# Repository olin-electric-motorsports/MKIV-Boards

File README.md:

# MKIV

```
$ vagrant up
$ vagrant ssh
```

```
$ kicad
```

```
$ freecad
```

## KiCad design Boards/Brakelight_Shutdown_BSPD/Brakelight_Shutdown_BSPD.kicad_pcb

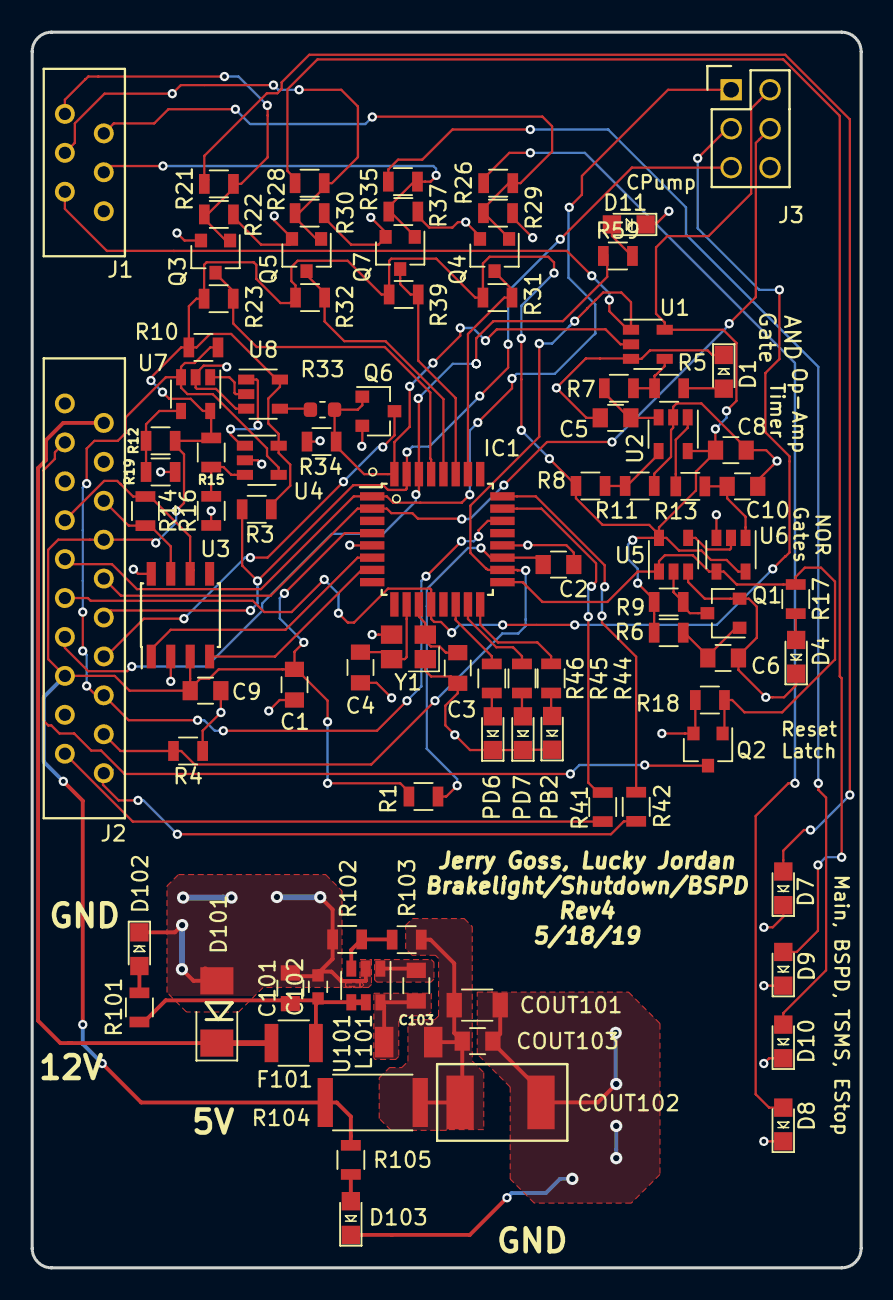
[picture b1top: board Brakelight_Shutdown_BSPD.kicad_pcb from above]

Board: 2 copper layers, 54.1 x 80.6 mm, 94 parts (0 on the bottom side), 66 nets.

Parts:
C1, C6, C8, C9, C101, C103: C_0.1uF; C_0805_OEM
C2: C_100pF; C_0805_OEM
C3, C4: C_30pF; C_0805_OEM
C5: C_10uF; C_0805_OEM
C10: C_1uF; C_0805_OEM
C102: C_2.2uF; C_0603
COUT101: C_22uF; C_1206_OEM
COUT102: C_33uF; Fuse_1812
COUT103: C_47uF; C_0805_OEM
D1, D4, D5, D7, D8, D9, D10, D11, D12, D13, D102, D103: LED_0805; LED_0805_OEM
D101: D_Zener_18V; DO-214AA
F101: F_500mA_16V; Fuse_1210
IC1: ATMEGA16M1; TQFP-32_7x7mm_Pitch0.8mm
J1: MM_F_RA_06; micromatch_female_ra_6
J2: MM_F_RA_20; micromatch_female_ra_20
J3: CONN_02X03; Pin_Header_Straight_2x03
L101: L_100uH
Q1, Q2, Q3, Q4, Q5, Q6, Q7: SSM3K333R; SOT-23F
R1: R_100; R_0805_OEM
R3: R_10k; R_0805_OEM
R4, R9, R22, R29, R30, R37, R103: R_100K; R_0805_OEM
R5, R14, R17, R41, R42, R44, R45, R46, R59, R101, R105: R_200; R_0805_OEM
R6, R8, R10, R11, R13, R15, R18, R23, R31, R32, R34, R39: R_10K; R_0805_OEM
R7: R_71.5K; R_0805_OEM
R12: R_2.2K; R_0805_OEM
R16, R21, R26, R28, R35: R_1K; R_0805_OEM
R19: R_499; R_0805_OEM
R33: R_0; R_0603_1608Metric
R102: R_25K; R_0805_OEM
R104: R_0_2512; R_2512_OEM
U1: SN74LVC1G08; SOT-23-5_OEM
U2, U4, U7: MCP6001; SOT-23-5_OEM
U3: CAN_Transceiver; SOIC-8_3.9x4.9mm_Pitch1.27mm_OEM
U5, U6: SN74LVC1G02; SOT-23-5_OEM
U8: SN74LVC1G32; SOT-23-5_OEM
U101: TPS560430YF; SOT-23-6_OEM
Y1: Crystal_SMD; Crystal_SMD_FA238

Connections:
+12V: D101.1, F101.2, J2.2
/BSPD_Current_Sense: IC1.18, J1.5, J2.18, R4.2, U1.1
/BSPD_Relay: J2.3, Q2.3
/BSPD_Relay_Sense: IC1.17, Q2.1, R17.1, R18.1, U5.1, U6.4
/Brake_Pressure_Sense: IC1.22, J2.16, R10.2, U4.4, U7.3
/Brakelight_Gate: IC1.32, Q6.1, R33.1, R34.1, U1.2
/Brakelight_LSD: J2.14, Q6.3
/CAN_high: J2.6, R14.1, U3.7
/CAN_low: J2.7, R14.2, U3.6
/Cooling_Pump_LSD: IC1.30, J2.13, R59.1
/LED_1: IC1.14, R46.1
/LED_2: IC1.15, R45.1
/LED_3: IC1.16, R44.1
/MISO: IC1.1, J2.9, J3.1
/MOSI: IC1.2, J2.10, J3.4
/RESET: IC1.31, J2.12, J3.5, R3.2
/RJ45_LED1: J2.19, R41.1
/RJ45_LED2: J2.20, R42.2
/RXCAN: IC1.7, U3.4
/SCK: IC1.12, J2.11, J3.3
/SS_BSPD_Pin: IC1.28, Q5.3, R32.2
/SS_E-Stop_Pin: IC1.26, Q4.3, R31.2
/SS_Main_Shutdown_Pin: IC1.29, Q3.3, R23.2
/SS_TSMS_Pin: IC1.27, Q7.3, R39.2
/Shutdown_Sense_BSPD: J1.3, Q5.1, R28.1, R30.1
/Shutdown_Sense_Estop: J1.2, Q4.1, R26.1, R29.1
/Shutdown_Sense_GLVMS: J1.1, Q3.1, R21.1, R22.1
/Shutdown_Sense_TSMS: J1.4, Q7.1, R35.1, R37.1
/TXCAN: IC1.6, U3.1
GND: C1.2, C2.2, C3.2, C4.2, C5.2, C6.2, C8.2, C9.2, C10.2, C101.2, C102.2, COUT101.2, COUT102.2, COUT103.2, D1.1, D4.1, D5.1, D7.1, D8.1, D9.1, D10.1, D11.1, D12.1, D13.1, D101.2, D102.1, D103.1, IC1.5, IC1.20, J2.1, J2.17, J3.6, Q1.2, Q2.2, Q3.2, Q4.2, Q5.2, Q6.2, Q7.2, R4.1, R11.2, R16.2, R18.2, R19.1, R22.2, R29.2, R30.2, R34.2, R37.2, R102.2, U1.3, U2.2, U3.2, U3.8, U4.2, U5.3, U6.3, U7.2, U8.3, U101.2, Y1.2, Y1.4
unnamed: C2.1, IC1.19, R1.2
unnamed: C3.1, IC1.11, Y1.1
unnamed: C4.1, IC1.10, Y1.3
unnamed: C5.1, R7.2, U2.3
unnamed: C6.1, Q1.1, R6.2
unnamed: C10.1, R13.1, U6.1
unnamed: C101.1, C102.1, F101.1, R101.1, U101.4, U101.5
unnamed: C103.1, L101.1, U101.6
unnamed: C103.2, U101.1
unnamed: COUT101.1, COUT102.1, COUT103.1, L101.2, R103.1, R104.1
unnamed: D1.2, R5.2
unnamed: D4.2, R17.2
unnamed: D5.2, R44.2
unnamed: D7.2, R21.2
unnamed: D8.2, R26.2
unnamed: D9.2, R28.2
unnamed: D10.2, R35.2
unnamed: D11.2, R59.2
unnamed: D12.2, R45.2
unnamed: D13.2, R46.2
unnamed: D102.2, R101.2
unnamed: D103.2, R105.2
unnamed: IC1.23, R41.2
unnamed: IC1.24, R42.1
unnamed: Q1.3, R9.1, U5.2
unnamed: R5.1, R7.1, U1.4
unnamed: R8.2, R11.1, U2.4
unnamed: R12.1, R19.2, U7.4
unnamed: R13.2, U2.1
unnamed: R15.2, R16.1, U4.3
unnamed: R33.2, U8.4
unnamed: R102.1, R103.2, U101.3
unnamed: U4.1, U8.1
unnamed: U5.4, U6.2
unnamed: U7.1, U8.2
VCC: C1.1, C8.1, C9.1, IC1.4, J2.8, J2.15, J3.2, R1.1, R3.1, R6.1, R8.1, R9.2, R10.1, R12.2, R15.1, R23.1, R31.1, R32.1, R39.1, R104.2, R105.1, U1.5, U2.5, U3.3, U4.5, U5.5, U6.5, U7.5, U8.5

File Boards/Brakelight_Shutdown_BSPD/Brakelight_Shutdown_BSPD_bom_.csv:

Component,Description,Part,References,Value,Footprint,Quantity Per PCB,Datasheet,Package,MPN,MFN,PurchasingLink,Link,Digi-key Part Number,Purchasing Link
1,"Capacitor, 0.1uF, 50V, 5%, 0805",C_0.1uF,C1 C6 C8 C9 C101 C103,C_0.1uF,C_0805_OEM,6,http://datasheets.avx.com/X7RDielectric.pdf,Value,478-3352-1-ND,Digi-Key DK,https://www.digikey.com/products/en?keywords=478-3352-1-ND,,,
2,"Capacitor, 100pF, 50V, 5%, 0805",C_100pF,C2,C_100pF,C_0805_OEM,1,https://content.kemet.com/datasheets/KEM_C1003_C0G_SMD.pdf,Value,399-1122-1-ND,Digi-Key,https://www.digikey.com/product-detail/en/kemet/C0805C101J5G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,,,
3,"Capacitor, 10uF, 10V, 10%, 0805",C_10uF,C5,C_10uF,C_0805_OEM,1,http://www.samsungsem.com/kr/support/product-search/mlcc/__i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,,1276-1052-1-ND,DK,https://www.digikey.com/product-detail/en/samsung-electro-me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,,,
4,"Capacitor, 1uF, 25V, 10%, 0805",C_1uF,C10,C_1uF,C_0805_OEM,1,http://www.samsungsem.com/kr/support/product-search/mlcc/__i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,,1276-2887-1-ND,DK,https://www.digikey.com/product-detail/en/samsung-electro-me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,,,
5,"Capacitor, 2.2uF, 10V, 10%, 0603",C_2.2uF,C102,C_2.2uF,C_0603_1608Metric,1,http://www.yageo.com/documents/recent/UPY-GPHC_X5R_4V-to-50V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,,311-1451-1-ND,DK,https://www.digikey.com/product-detail/en/yageo/CC0603KRX5R6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,,,
6,"Capacitor, 30pF, 50V, 5%, 0805",C_30pF,C3 C4,C_30pF,C_0805_OEM,2,https://media.digikey.com/pdf/Data%20Sheets/Samsung%20PDFs/C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,Value,1276-1130-1-ND,Digi-Key,https://www.digikey.com/product-detail/en/samsung-electro-me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,,,
7,"Capacitor, 22uF, 16V, 20%, 1206",C_22uF,COUT101,C_22uF,C_1206_OEM,1,https://product.tdk.com/info/en/catalog/datasheets/mlcc_comm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,,445-11693-1-ND,DK,https://www.digikey.com/product-detail/en/tdk-corporation/C3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,,,
8,,C_33uF,COUT102,C_33uF,Fuse_1812,1,https://product.tdk.com/info/en/catalog/datasheets/mlcc_comm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,,445-3924-1-ND,C4532X7R1C336M250KC,https://www.digikey.com/product-detail/en/tdk-corporation/C4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,,,
9,"Capacitor, 47uF, 6.3V, 20%, 0805",C_47uF,COUT103,C_47uF,C_0805_OEM,1,http://www.samsungsem.com/kr/support/product-search/mlcc/__i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,,1276-6467-1-ND,DK,https://www.digikey.com/product-detail/en/samsung-electro-me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,,,
10,"Diode, Zener, 18V, 5W, 5%",D_Zener_18V,D101,D_Zener_18V,DO-214AA,1,http://www.mccsemi.com/up_pdf/SMBJ5338B-SMBJ5388B(SMB).pdf,,SMBJ5355B-TPMSCT-ND,DK,https://www.digikey.com/products/en?keywords=SMBJ5355B-TPMSCT-ND,,,
11,"LED, Green, 2.2V, 20mA, 0805",LED_0805,D1 D4 D5 D7 D8 D9 D10 D11 D12 D13 D102 D103,LED_0805,LED_0805_OEM,12,http://www.osram-os.com/Graphics/XPic9/00078860_0.pdf,,475-1410-1-ND,DK,https://www.digikey.com/products/en?keywords=475-1410-1-ND,,,
12,"Fuse, PTC, 500mA, 16V, 1210",F_500mA_16V,F101,F_500mA_16V,Fuse_1210,1,https://belfuse.com/resources/CircuitProtection/datasheets/0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,,507-1786-1-ND,DK,https://www.digikey.com/product-detail/en/bel-fuse-inc/0ZCH0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,,,
13,"Microcontroller, 8-bit, 1KB RAM, 16KB Flash",ATMEGA16M1,IC1,ATMEGA16M1,TQFP-32_7x7mm_Pitch0.8mm,1,http://www.atmel.com/Images/Atmel-8209-8-bit%20AVR%20ATmega1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,Value,ATMEGA16M1-AU-ND,Digi-Key,https://www.digikey.com/product-detail/en/atmel/ATMEGA16M1-A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,,,
14,"Connector header through hole 2x3 0.100"" (2.54mm)",CONN_02X03,J3,CONN_02X03,Pin_Header_Straight_2x03,1,http://portal.fciconnect.com/Comergent//fci/drawing/67996.pdf,Value,609-3234-ND,Digi-Key,https://www.digikey.com/product-detail/en/amphenol-fci/67997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,,,
15,Micro-MaTch connector 6 pin female right angle,MM_F_RA_06,J1,MM_F_RA_06,micromatch_female_ra_6,1,http://www.te.com/commerce/DocumentDelivery/DDEController?Ac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,,338070-6,TE,http://www.te.com/usa-en/product-338070-6.html,,,
16,Micro-MaTch connector 20 pin female right angle,MM_F_RA_20,J2,MM_F_RA_20,micromatch_female_ra_20,1,http://www.te.com/commerce/DocumentDelivery/DDEController?Ac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,,2-338070-0,TE,http://www.te.com/usa-en/product-2-338070-0.html,,,
17,,L_100uH,L101,L_100uH,L_100uH,1,https://product.tdk.com/info/en/catalog/datasheets/inductor_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,,445-15759-1-ND,Digikey,,https://www.digikey.com/product-detail/en/tdk-corporation/NL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,,
18,"MOSFET, N-channel, 30V, 6A",SSM3K333R,Q1 Q2 Q3 Q4 Q5 Q6 Q7,SSM3K333R,SOT-23F,7,https://drive.google.com/drive/folders/0B-V-iZf33Y4GNzhDQTJZanJRbVk,,SSM3K333RLFCT-ND,DK,https://www.digikey.com/product-detail/en/toshiba-semiconduc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,,,
19,"Resistor, 0 ohm jumper, 0.1W, 0603",R_0,R33,R_0,R_0603_1608Metric,1,http://industrial.panasonic.com/www-cgi/jvcr13pz.cgi?E+PZ+3+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,,P0.0GCT-ND,DK,https://www.digikey.com/product-detail/en/panasonic-electron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,,,
20,"Resistor, 0 ohm jumper, 3W, 2512",R_0_2512,R104,R_0_2512,R_2512_OEM,1,http://www.te.com/commerce/DocumentDelivery/DDEController?Ac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,,A121322CT-ND,DK,https://www.digikey.com/products/en?keywords=A121322CT-ND,,,
21,"Resistor, 100, 0.25W, 1%, 0805",R_100,R1,R_100,R_0805_OEM,1,https://www.seielect.com/Catalog/SEI-rncp.pdf,Value,RNCP0805FTD100RCT-ND,Digi-Key,https://www.digikey.com/products/en?keywords=RNCP0805FTD100RCT-ND,,,
22,"Resistor, 100K, 0.125W, 1%, 0805",R_100K,R2 R4 R9 R22 R29 R30 R37 R103,R_100K,R_0805_OEM,8,https://industrial.panasonic.com/cdbs/www-data/pdf/RDA0000/A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,,P100KCCT-ND,DK,https://www.digikey.com/product-detail/en/panasonic-electron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,,,
23,"Resistor, 10K, 0.25W, 1%, 0805",R_10K,R3 R6 R8 R11 R13 R18 R23 R24 R25 R27 R31 R32 R34 R39,R_10k,R_0805_OEM,14,http://www.bourns.com/data/global/pdfs/CRS.pdf,Value,CRS0805-FX-1002ELFCT-ND,Digi-Key DK,https://www.digikey.com/products/en?keywords=CRS0805-FX-1002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,,,
24,"Resistor, 1K, 0.25W, 1%, 0805",R_1K,R21 R26 R28 R35,R_1K,R_0805_OEM,4,https://www.seielect.com/Catalog/SEI-rncp.pdf,,RNCP0805FTD1K00CT-ND,DK,https://www.digikey.com/products/en?keywords=RNCP0805FTD1K00CT-ND,,,
25,"Resistor, 200, 0.125W, 5%, 0805",R_200,R5 R14 R17 R41 R42 R44 R45 R46 R101 R105,R_200,R_0805_OEM,10,https://www.seielect.com/Catalog/SEI-RMCF_RMCP.pdf,Value,RMCF0805JT200RCT-ND,DK Digi-Key,https://www.digikey.com/products/en?keywords=RMCF0805JT200RCT-ND,,,
26,,R_25K,R102,R_25K,R_0805_OEM,1,https://www.te.com/commerce/DocumentDelivery/DDEController?A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,,,A124124CT-ND,https://www.digikey.com/product-detail/en/te-connectivity-pa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,,CPF-A-0805B25KE,
27,"Resistor, 1.07K, 0.125W, 0.1%, 0805",R_1.07K,R7,R_71.5K,R_0805_OEM,1,https://industrial.panasonic.com/cdbs/www-data/pdf/RDM0000/A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,,P1.07KDACT-ND,DK,,,,
28,"High speed CAN transceiver, 1Mb/s",MCP2561-E_SN,U3,CAN_Transceiver,SOIC-8_3.9x4.9mm_Pitch1.27mm_OEM,1,http://www.microchip.com/mymicrochip/filehandler.aspx?ddocna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,Value,MCP2561-E/SN-ND,Digi-Key,https://www.digikey.com/products/en?keywords=mcp2561-e%2Fsn,,,
29,"Op-amp, general purpose",MCP6001,U2 U7,MCP6001,SOT-23-5_OEM,2,http://ww1.microchip.com/downloads/en/DeviceDoc/21733j.pdf,,MCP6001T-I/OTCT-ND,DK,https://www.digikey.com/product-detail/en/microchip-technolo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,,,
30,Single channel positive logic NOR gate,SN74LVC1G02,U5 U6,SN74LVC1G02,SOT-23-5_OEM,2,http://www.ti.com/lit/ds/symlink/sn74lvc1g02.pdf,,296-11598-1-ND,DK,https://www.digikey.com/product-detail/en/texas-instruments/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,,,
31,Single channel positive logic AND gate,SN74LVC1G08,U1,SN74LVC1G08,SOT-23-5_OEM,1,http://www.ti.com/lit/ds/symlink/sn74lvc1g08.pdf,,296-11602-1-ND,DK,https://www.digikey.com/product-detail/en/texas-instruments/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,,,
32,,TPS560430YF,U101,TPS560430YF,SOT-23-6_Handsoldering,1,http://www.ti.com/lit/ds/symlink/tps560430.pdf,,TPS560430YFDBVR,TPS560430YFDBVR-ND,,,,https://www.digikey.com/product-detail/en/texas-instruments/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
33,CRYSTAL 16.0000MHZ 18PF SMD,Crystal_SMD,Y1,Crystal_SMD,Crystal_SMD_FA238,1,https://support.epson.biz/td/api/doc_check.php?dl=brief_FA-2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,Value,SER3686CT-ND,Digi-Key,https://www.digikey.com/products/en?keywords=SER3686CT-ND,,,





Component Groups:,33
Component Count:,90
Fitted Components:,90
Number of PCBs:,1
Total components:,90
Schematic Version:,
Schematic Date:,
BoM Date:,Thu 09 May 2019 08:50:00 PM EDT
Schematic Source:,/home/jerry/OlinCollege/Formula/MKIV-Boards/Boards/Brakelight_Shutdown_BSPD/Brakelight_Shutdown_BSPD.sch
KiCad Version:,Eeschema 5.0.2-bee76a0~70~ubuntu18.04.1

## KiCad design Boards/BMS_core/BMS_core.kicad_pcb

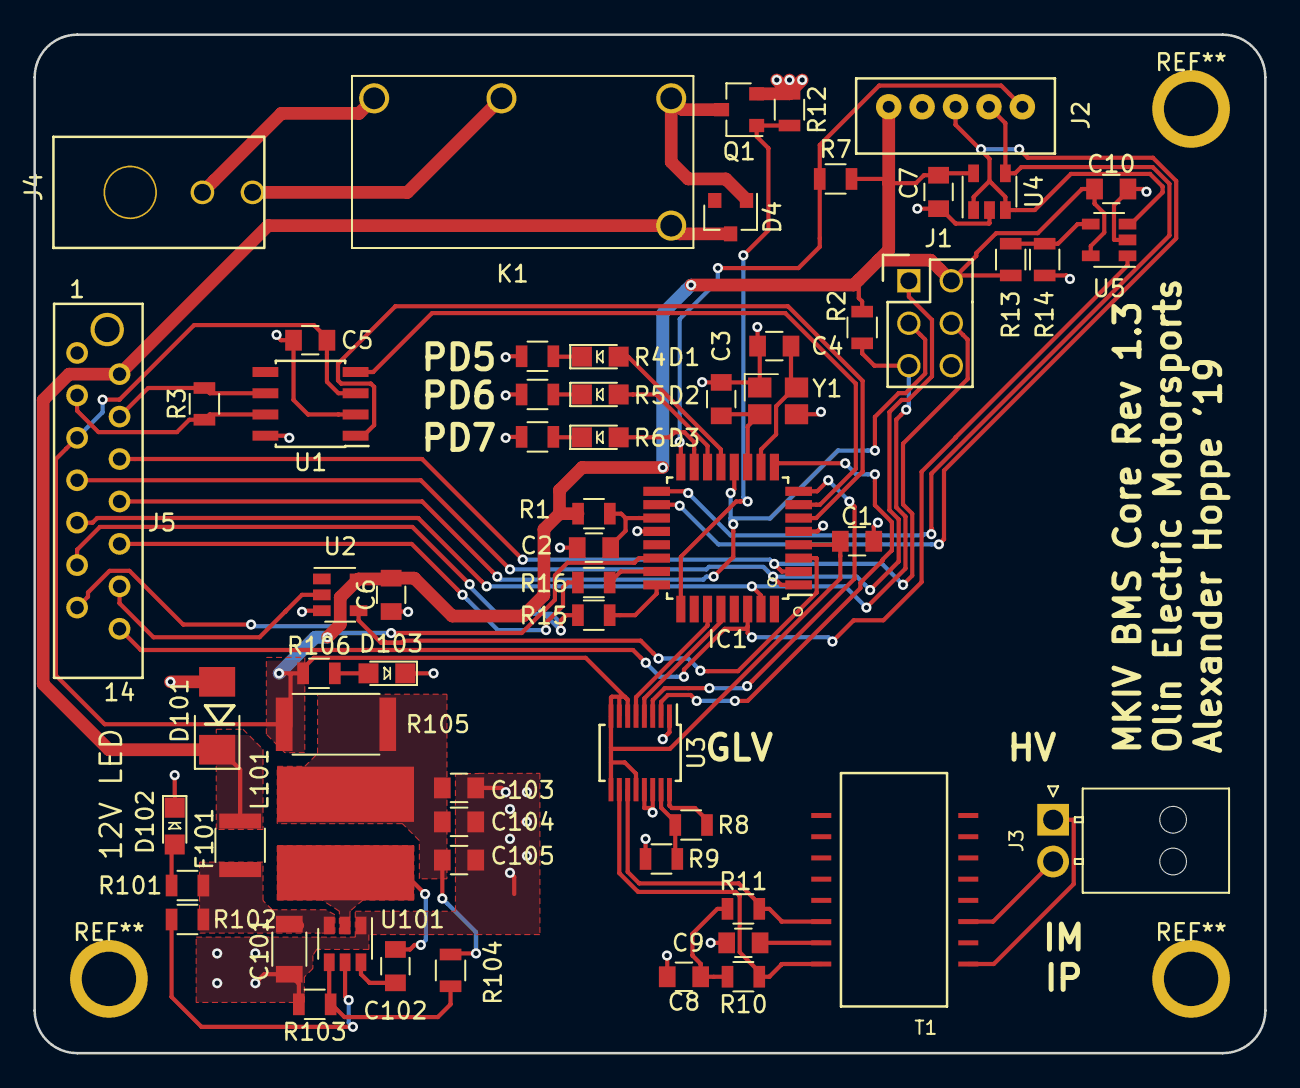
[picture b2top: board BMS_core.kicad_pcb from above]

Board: 2 copper layers, 73.7 x 61.0 mm, 62 parts (0 on the bottom side), 56 nets.

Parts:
C1, C5, C6, C7, C10, C102, C105: C_0.1uF; C_0805_OEM
C2: C_100pF; C_0805_OEM
C3, C4: C_30pF; C_0805_OEM
C8, C9: C_10nF; C_0805_OEM
C101: C_22uF; C_1206_OEM
C103: C_47uF; C_0805_OEM
C104: C_1uF; C_0805_OEM
D1, D2, D3, D102, D103: LED_0805; LED_0805_OEM
D4: BAS40-00; SOT-23
D101: D_Zener_18V; DO-214AA
F101: 500mA; Fuse_1210
IC1: ATMEGA16M1; TQFP-32_7x7mm_Pitch0.8mm
J1: CONN_02X03; Pin_Header_Straight_2x03
J2: B5B-PH-K-S
J3: NanoFit_2; NanoFit_Molex_1x02x2.50mm_Angled_OEM
J4: MicroFit_RA_V_2
J5: MM_F_VT_14; micromatch_female_vert_14
K1: G5Q-1A4-DC5-5V; Relay_SPST_OMRON-G5Q-1A4_OEM
L101: L_4.7uH; 4.7uH_Inductor_OEM
Q1: SSM3K333R; SOT-23F
R1: R_100; R_0805_OEM
R2, R7, R12, R102, R103: R_10K; R_0805_OEM
R3, R4, R5, R6, R15, R16, R106: R_200; R_0805_OEM
R8: R_3.01K; R_0805_OEM
R9, R101: R_1K; R_0805_OEM
R10, R11: R_60.4; R_0805_OEM
R13: R_17.4K_0.1; R_0805_OEM
R14: R_1K_0.1; R_0805_OEM
R104: R_54.9K; R_0805_OEM
R105: R_0_2512; R_2512_OEM
T1: T_LAN_7490100111A
U1: MCP2561-E_SN; SOIC-8_3.9x4.9mm_Pitch1.27mm_OEM
U2: SN74LVC1G17; SOT-23-5
U3: LTC6820HMS; MSOP-16_3x4mm_P0.5mm
U4, U5: MCP6001; SOT-23-5_OEM
U101: TPS561201; SOT-23-6_OEM
Y1: Crystal_SMD; Crystal_SMD_FA238

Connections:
+12V: D4.3, D101.1, F101.1, J5.2, K1.5
/BMS_SENSE: IC1.22, J5.13
/BSPD_CURRENT: IC1.30, J5.14, U5.1
/CANH: J5.3, R3.1, U1.7
/CANL: J5.4, R3.2, U1.6
/CS_iso: IC1.27, U3.5
/FAN_PWM: J5.12, U2.2
/FAN_PWM_RAW: IC1.3, U2.4
/MISO: IC1.1, J1.1, J5.7
/MISO_iso: IC1.8, U3.3
/MOSI: IC1.2, J1.4, J5.6
/MOSI_iso: IC1.9, U3.2
/PROG_1: D1.2, IC1.13
/PROG_2: D2.2, IC1.14
/PROG_3: D3.2, IC1.15
/RELAY_DRIVE: IC1.25, Q1.1, R12.2
/RESET: IC1.31, J1.5, J5.9, R2.2
/RJ45_LED1: J5.10, R16.1
/RJ45_LED2: J5.11, R15.1
/RXCAN: IC1.7, U1.4
/SCK: IC1.12, J1.3, J5.8
/SCK_iso: IC1.28, U3.4
/SHDN_IN(MAIN_PACK->BMS): J4.1, K1.3
/SHDN_OUT(BMS->IMD): J4.2, K1.2
/TXCAN: IC1.6, U1.1
/VOUT: IC1.18, J2.3, U4.1, U4.3, U5.3
/VREF: IC1.17, J2.4, U4.4
/~OCD: IC1.16, J2.5, R7.2
GND: C1.2, C2.2, C3.2, C4.2, C5.2, C6.1, C7.2, C8.2, C9.2, C10.2, C101.2, C103.2, C104.2, C105.2, D101.2, D102.1, D103.1, IC1.5, IC1.20, J1.6, J2.2, J5.1, Q1.2, R4.2, R5.2, R6.2, R9.2, R12.1, R14.2, R103.2, U1.2, U1.8, U2.3, U3.1, U3.13, U3.14, U4.2, U5.2, U101.1, Y1.2, Y1.4
unnamed: C2.1, IC1.19, R1.2
unnamed: C3.1, IC1.11, Y1.1
unnamed: C4.1, IC1.10, Y1.3
unnamed: C8.1, R10.2, R11.1
unnamed: C9.1, T1.15
unnamed: C101.1, F101.2, R101.1, R102.2, U101.3
unnamed: C102.1, U101.6
unnamed: C102.2, L101.1, U101.2
unnamed: C103.1, C104.1, C105.1, L101.2, R104.2, R105.2
unnamed: D1.1, R4.1
unnamed: D2.1, R5.1
unnamed: D3.1, R6.1
unnamed: D4.1, K1.1, Q1.3
unnamed: D102.2, R101.2
unnamed: D103.2, R106.2
unnamed: IC1.23, R16.2
unnamed: IC1.24, R15.2
unnamed: J3.1, T1.1
unnamed: J3.2, T1.3
unnamed: R8.1, U3.16
unnamed: R8.2, R9.1, U3.15
unnamed: R10.1, T1.16, U3.10
unnamed: R11.2, T1.14, U3.11
unnamed: R13.2, R14.1, U5.4
unnamed: R102.1, U101.5
unnamed: R103.1, R104.1, U101.4
VCC: C1.1, C5.1, C6.2, C7.1, C10.1, IC1.4, J1.2, J2.1, J5.5, R1.1, R2.1, R7.1, R13.1, R105.1, R106.1, U1.3, U2.5, U3.6, U3.7, U3.8, U3.9, U3.12, U4.5, U5.5

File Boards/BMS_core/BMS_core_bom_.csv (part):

Component,Description,Part,References,Value,Footprint,Quantity Per PCB,Datasheet,Package,MPN,MFN,PurchasingLink
1,"Capacitor, 0.1uF, 50V, 5%, 0805",C_0.1uF,C1 C5 C6 C7 C10 C102 C105,C_0.1uF,C_0805_OEM,7,http://datasheets.avx.com/X7RDielectric.pdf,Value,478-3352-1-ND,Digi-Key DK,https://www.digikey.com/products/en?keywords=478-3352-1-ND
2,"Capacitor, 100pF, 50V, 5%, 0805",C_100pF,C2,C_100pF,C_0805_OEM,1,https://content.kemet.com/datasheets/KEM_C1003_C0G_SMD.pdf,Value,399-1122-1-ND,Digi-Key,https://www.digikey.com/product-detail/en/kemet/C0805C101J5G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
3,"Capacitor, 10nF 50V X7R 0805",C_10nF,C8 C9,C_10nF,C_0805_OEM,2,http://www.samsungsem.com/kr/support/product-search/mlcc/__i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,,1276-1015-1-ND,DK,https://www.digikey.com/product-detail/en/samsung-electro-me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
4,"Capacitor, 1uF, 25V, 10%, 0805",C_1uF,C104,C_1uF,C_0805_OEM,1,http://datasheets.avx.com/X7RDielectric.pdf,Value,478-10487-1-ND,Digi-Key,https://www.digikey.com/product-detail/en/avx-corporation/08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
5,"Capacitor, 22uF, 16V, 20%, 1206",C_22uF,C101,C_22uF,C_1206_OEM,1,http://www.samsungsem.com/kr/support/product-search/mlcc/__i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,Value,1276-2725-1-ND,Digi-Key,https://www.digikey.com/products/en?keywords=1276-2725-1-ND
6,"Capacitor, 30pF, 50V, 5%, 0805",C_30pF,C3 C4,C_30pF,C_0805_OEM,2,https://media.digikey.com/pdf/Data%20Sheets/Samsung%20PDFs/C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,Value,1276-1130-1-ND,Digi-Key,https://www.digikey.com/product-detail/en/samsung-electro-me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
7,"Capacitor, 47uF, 6.3V, 20%, 0805",C_47uF,C103,C_47uF,C_0805_OEM,1,http://www.yuden.co.jp/productdata/catalog/en/mlcc_all_e.pdf,Value,587-4280-1-ND,Digi-Key,https://www.digikey.com/product-detail/en/taiyo-yuden/JMK212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
8,"Schottky Diode, 40V, 120mA, SOT23",BAS40-00,D4,BAS40-00,SOT-23,1,https://assets.nexperia.com/documents/data-sheet/BAS40_1PSXX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,,1727-4234-1-ND,DK,https://www.digikey.com/product-detail/en/nexperia-usa-inc/B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
9,"Diode, Zener, 18V, 5W, 5%",D_Zener_18V,D101,D_Zener_18V,DO-214AA,1,http://www.mccsemi.com/up_pdf/SMBJ5338B-SMBJ5388B(SMB).pdf,DO-214AA (SMB),SMBJ5355B-TPMSCT-ND,Digi-Key,https://www.digikey.com/products/en?keywords=SMBJ5355B-TPMSCT-ND
10,"LED, Green, 2.2V, 20mA, 0805",LED_0805,D1 D2 D3 D102 D103,LED_0805,LED_0805_OEM,5,http://www.osram-os.com/Graphics/XPic9/00078860_0.pdf,Value,475-1410-1-ND,DK Digi-Key,https://www.digikey.com/products/en?keywords=475-1410-1-ND
11,"Fuse, PTC, 500mA, 16V, 1210",F_500mA_16V,F101,500mA,Fuse_1210,1,https://belfuse.com/resources/CircuitProtection/datasheets/0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,Value,507-1786-1-ND,Digi-Key,https://www.digikey.com/product-detail/en/bel-fuse-inc/0ZCH0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
12,"Microcontroller, 8-bit, 1KB RAM, 16KB Flash",ATMEGA16M1,IC1,ATMEGA16M1,TQFP-32_7x7mm_Pitch0.8mm,1,http://www.atmel.com/Images/Atmel-8209-8-bit%20AVR%20ATmega1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,Value,ATMEGA16M1-AU-ND,Digi-Key,https://www.digikey.com/product-detail/en/atmel/ATMEGA16M1-A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
13,"Connector Header Through Hole 5 position 0.079"" (2.00mm)",B5B-PH-K-S,J2,B5B-PH-K-S,B5B-PH-K-S,1,http://www.jst-mfg.com/product/pdf/eng/ePH.pdf,,455-1707-ND,DK,https://www.digikey.com/product-detail/en/jst-sales-america-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
14,"Connector header through hole 2x3 0.100"" (2.54mm)",CONN_02X03,J1,CONN_02X03,Pin_Header_Straight_2x03,1,http://portal.fciconnect.com/Comergent//fci/drawing/67996.pdf,Value,609-3234-ND,Digi-Key,https://www.digikey.com/product-detail/en/amphenol-fci/67997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
15,Micro-MaTch connector 14 pin female vertical,MM_F_VT_14,J5,MM_F_VT_14,micromatch_female_vert_14,1,http://www.te.com/commerce/DocumentDelivery/DDEController?Ac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,,1-338068-4,TE,http://www.te.com/global-en/product-1-338068-4.html
16,"Micro-Fit Connector, Right Angle 2 circuit",MicroFit_RA_R_2,J4,MicroFit_RA_R_2,MicroFit_RA_2,1,https://www.molex.com/pdm_docs/sd/436500201_sd.pdf,,WM1865-ND,DK,https://www.digikey.com/product-detail/en/molex/0436500201/W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
17,Nano-Fit connector 2 pin right angle,NanoFit_2,J3,NanoFit_2,NanoFit_Molex_1x02x2.50mm_Angled_OEM,1,https://www.molex.com/pdm_docs/sd/1053131102_sd.pdf,,WM14972-ND,DK,https://www.digikey.com/products/en/connectors-interconnects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
18,"Relay, SPST-NO, Switch 10A/30V, Coil 40mA/5V",G5Q-1A4-DC5-5V,K1,G5Q-1A4-DC5-5V,Relay_SPST_OMRON-G5Q-1A4_OEM,1,http://omronfs.omron.com/en_US/ecb/products/pdf/en-g5q.pdf,,Z3632-ND,DK,https://www.digikey.com/product-detail/en/omron-electronics-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
19,"Inductor, 4.7uH, 4.4A, 25mOhm, 20%",L_4.7uH,L101,L_4.7uH,4.7uH_Inductor_OEM,1,https://product.tdk.com/info/en/documents/wdcatalog/withdraw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,Value,445-6583-1-ND,Digi-Key,https://www.digikey.com/product-detail/en/tdk-corporation/VL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
20,"MOSFET, N-channel, 30V, 6A",SSM3K333R,Q1,SSM3K333R,SOT-23F,1,https://drive.google.com/drive/folders/0B-V-iZf33Y4GNzhDQTJZanJRbVk,,SSM3K333RLFCT-ND,DK,https://www.digikey.com/product-detail/en/toshiba-semiconduc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
21,"Resistor, 0 ohm jumper, 3W, 2512",R_0_2512,R105,R_0_2512,R_2512_OEM,1,http://www.te.com/commerce/DocumentDelivery/DDEController?Ac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,,A121322CT-ND,DK,https://www.digikey.com/products/en?keywords=A121322CT-ND
22,"Resistor, 100, 0.25W, 1%, 0805",R_100,R1,R_100,R_0805_OEM,1,https://www.seielect.com/Catalog/SEI-rncp.pdf,Value,RNCP0805FTD100RCT-ND,Digi-Key,https://www.digikey.com/products/en?keywords=RNCP0805FTD100RCT-ND
23,"Resistor, 10K, 0.25W, 1%, 0805",R_10K,R2 R7 R12 R102 R103,R_10K,R_0805_OEM,5,http://www.bourns.com/data/global/pdfs/CRS.pdf,,CRS0805-FX-1002ELFCT-ND,DK,https://www.digikey.com/products/en?keywords=CRS0805-FX-1002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
24,"Resistor, 17.4K, 0.125W, 0.1%, 0805",R_17.4K_0.1,R13,R_17.4K_0.1,R_0805_OEM,1,https://industrial.panasonic.com/cdbs/www-data/pdf/RDM0000/A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,,P17.4KDACT-ND,DK,https://www.digikey.com/product-detail/en/panasonic-electron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
25,"Resistor, 1K, 0.25W, 1%, 0805",R_1K,R9 R101,R_1K,R_0805_OEM,2,https://www.seielect.com/Catalog/SEI-rncp.pdf,,RNCP0805FTD1K00CT-ND,DK,https://www.digikey.com/products/en?keywords=RNCP0805FTD1K00CT-ND
26,"Resistor, 1K, 0.125W, 0.1%, 0805",R_1K_0.1,R14,R_1K_0.1,R_0805_OEM,1,https://industrial.panasonic.com/cdbs/www-data/pdf/RDM0000/A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,,P1.0KDACT-ND,DK,https://www.digikey.com/product-detail/en/panasonic-electron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
27,"Resistor, 200, 0.125W, 5%, 0805",R_200,R3 R4 R5 R6 R106,R_200,R_0805_OEM,5,https://www.seielect.com/Catalog/SEI-RMCF_RMCP.pdf,Value,RMCF0805JT200RCT-ND,Digi-Key DK,https://www.digikey.com/products/en?keywords=RMCF0805JT200RCT-ND
28,"Resistor, 3.01K, 0.125W, 1%, 0805",R_3.01K,R8,R_3.01K,R_0805_OEM,1,http://www.yageo.com.tw/exep/pages/download/literatures/PYu-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,,311-3.01KCRCT-ND,DK,https://www.digikey.com/products/en?keywords=311-3.01KCRCT-ND
29,"Resistor, 54.9, 0.125W, 1%, 0805",R_54.9K,R104,R_54.9K,R_0805_OEM,1,https://industrial.panasonic.com/cdbs/www-data/pdf/RDA0000/A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,,311-54.9KCRCT-ND,DK,https://www.digikey.com/product-detail/en/yageo/RC0805FR-075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
30,"Resistor, 60.4, 0.1%, 0.125W, 0805",R_60.4,R10 R11,R_60.4,R_0805_OEM,2,https://industrial.panasonic.com/cdbs/www-data/pdf/RDM0000/A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,,P60.4DACT-ND,DK,https://www.digikey.com/product-detail/en/panasonic-electron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
31,Transformer LAN 10/100 base-T,T_LAN_7490100111A,T1,T_LAN_7490100111A,T_LAN_7490100111A,1,https://katalog.we-online.de/pbs/datasheet/7490100111A.pdf,,732-5711-1-ND,DK,https://www.digikey.com/product-detail/en/wurth-electronics-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
32,isoSPI Isolated Communications Interface,LTC6820HMS,U3,LTC6820HMS,MSOP-16_3x4mm_P0.5mm,1,https://www.analog.com/media/en/technical-documentation/data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,,LTC6820HMS#TRPBFCT-ND,DK,https://www.digikey.com/product-detail/en/linear-technology-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
33,"High speed CAN transceiver, 1Mb/s",MCP2561-E_SN,U1,MCP2561-E_SN,SOIC-8_3.9x4.9mm_Pitch1.27mm_OEM,1,http://www.microchip.com/mymicrochip/filehandler.aspx?ddocna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,,MCP2561-E/SN-ND,DK,https://www.digikey.com/products/en?keywords=mcp2561-e%2Fsn
34,"Op-amp, general purpose",MCP6001,U4 U5,MCP6001,SOT-23-5_OEM,2,http://ww1.microchip.com/downloads/en/DeviceDoc/21733j.pdf,,MCP6001T-I/OTCT-ND,DK,https://www.digikey.com/product-detail/en/microchip-technolo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
35,Single schmitt-trigger buffer,SN74LVC1G17,U2,SN74LVC1G17,SOT-23-5,1,http://www.ti.com/lit/ds/symlink/sn74lvc1g17.pdf,,296-11933-1-ND,DK,https://www.digikey.com/product-detail/en/texas-instruments/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

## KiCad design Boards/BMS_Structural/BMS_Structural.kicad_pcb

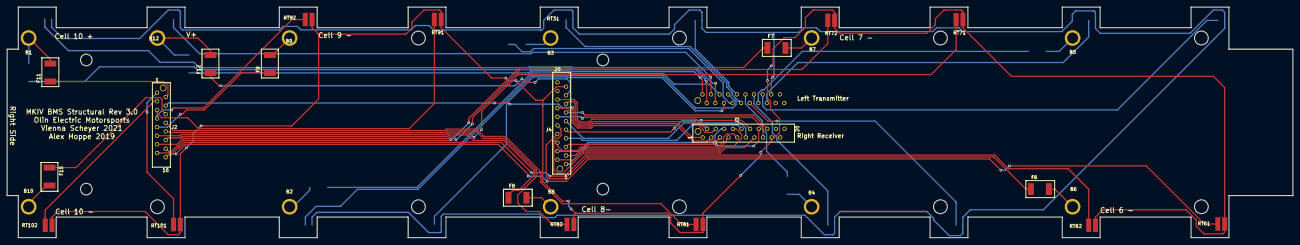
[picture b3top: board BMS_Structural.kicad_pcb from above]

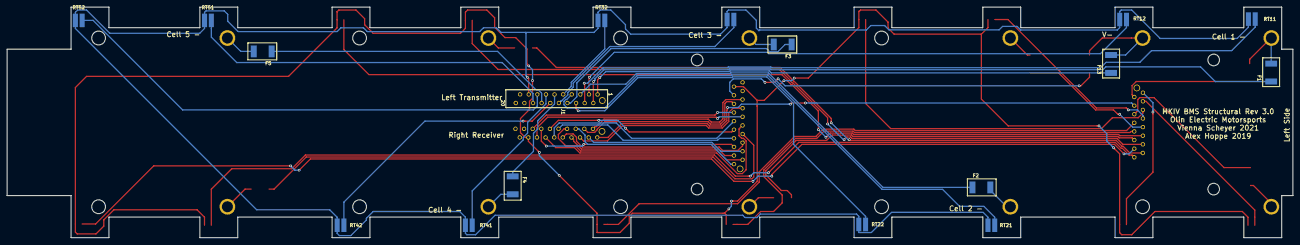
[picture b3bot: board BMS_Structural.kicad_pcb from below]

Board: 2 copper layers, 379.3 x 68.0 mm, 48 parts (17 on the bottom side), 62 nets.

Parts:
B1, B2, B3, B4, B5, B6, B7, B8, B9, B10, B12: Bolt_connect_4-40; Bolt_connect_4-40_round
F1, F2, F3, F4, F5, F6, F7, F8, F9, F10, F11, F12, F13: 200mA_Fuse; Fuse_1812
J1, J3, J4: MM_F_VT_20; micromatch_female_vert_20
J2: MM_F_VT_16; micromatch_female_vert_16
RT11, RT12, RT21, RT22, RT31, RT32, RT41, RT42, RT51, RT52, RT61, RT62, RT71, RT72, RT81, RT82, RT91, RT92, RT101, RT102: Thermistor

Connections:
/CELL0_VOLT_L: F1.1, J1.2
/CELL0_VOLT_R: J3.2, J4.16
/CELL1_VOLT_L: F2.1, J1.5
/CELL1_VOLT_R: J3.5, J4.14
/CELL2_VOLT_L: F3.1, J1.8
/CELL2_VOLT_R: J3.8, J4.2
/CELL3_VOLT_L: F4.1, J1.11
/CELL3_VOLT_R: J3.11, J4.11
/CELL4_VOLT_L: F5.1, J1.14
/CELL4_VOLT_R: J3.14, J4.5
/CELL5_VOLT_R: F6.1, J4.8
/CELL6_VOLT_R: F7.1, J2.15
/CELL7_VOLT_R: F8.1, J2.12
/CELL8_VOLT_R: F9.1, J2.9
/CELL9_VOLT_R: F10.1, J2.6
/CELL10_VOLT_R: F11.1, J2.2
/GND_L: J1.17, RT11.2, RT12.2, RT21.2, RT22.2, RT31.2, RT32.2, RT41.2, RT42.2, RT51.2, RT52.2
/GND_R: J3.17, J4.19, RT61.2, RT62.2, RT71.2, RT72.2, RT81.2, RT82.2, RT91.2, RT92.2, RT101.2, RT102.2
/MODULE1_TEMP1_L: J1.4, RT11.1
/MODULE1_TEMP1_R: J3.4, J4.15
/MODULE1_TEMP2_L: J1.3, RT12.1
/MODULE1_TEMP2_R: J3.3, J4.4
/MODULE2_TEMP1_L: J1.7, RT21.1
/MODULE2_TEMP1_R: J3.7, J4.3
/MODULE2_TEMP2_L: J1.6, RT22.1
/MODULE2_TEMP2_R: J3.6, J4.1
/MODULE3_TEMP1_L: J1.10, RT31.1
/MODULE3_TEMP1_R: J3.10, J4.7
/MODULE3_TEMP2_L: J1.9, RT32.1
/MODULE3_TEMP2_R: J3.9, J4.6
/MODULE4_TEMP1_L: J1.13, RT41.1
/MODULE4_TEMP1_R: J3.13, J4.10
/MODULE4_TEMP2_L: J1.12, RT42.1
/MODULE4_TEMP2_R: J3.12, J4.9
/MODULE5_TEMP1_L: J1.16, RT51.1
/MODULE5_TEMP1_R: J3.16, J4.13
/MODULE5_TEMP2_L: J1.15, RT52.1
/MODULE5_TEMP2_R: J3.15, J4.12
/MODULE6_TEMP1_R: J2.14, RT61.1
/MODULE6_TEMP2_R: J2.16, RT62.1
/MODULE7_TEMP1_R: J2.11, RT71.1
/MODULE7_TEMP2_R: J2.13, RT72.1
/MODULE8_TEMP1_R: J2.8, RT81.1
/MODULE8_TEMP2_R: J2.10, RT82.1
/MODULE9_TEMP1_R: J2.5, RT91.1
/MODULE9_TEMP2_R: J2.7, RT92.1
/MODULE10_TEMP1_R: J2.1, RT101.1
/MODULE10_TEMP2_R: J2.3, RT102.1
/V+_R: F12.1, J4.17
/V-_L: F13.1, J1.1
/V-_R: J2.4, J3.1
unnamed: B1.1, F1.2, F11.2
unnamed: B2.1, F2.2
unnamed: B3.1, F3.2
unnamed: B4.1, F4.2
unnamed: B5.1, F5.2
unnamed: B6.1, F6.2
unnamed: B7.1, F7.2
unnamed: B8.1, F8.2
unnamed: B9.1, F9.2
unnamed: B10.1, F10.2
unnamed: B12.1, F12.2, F13.2

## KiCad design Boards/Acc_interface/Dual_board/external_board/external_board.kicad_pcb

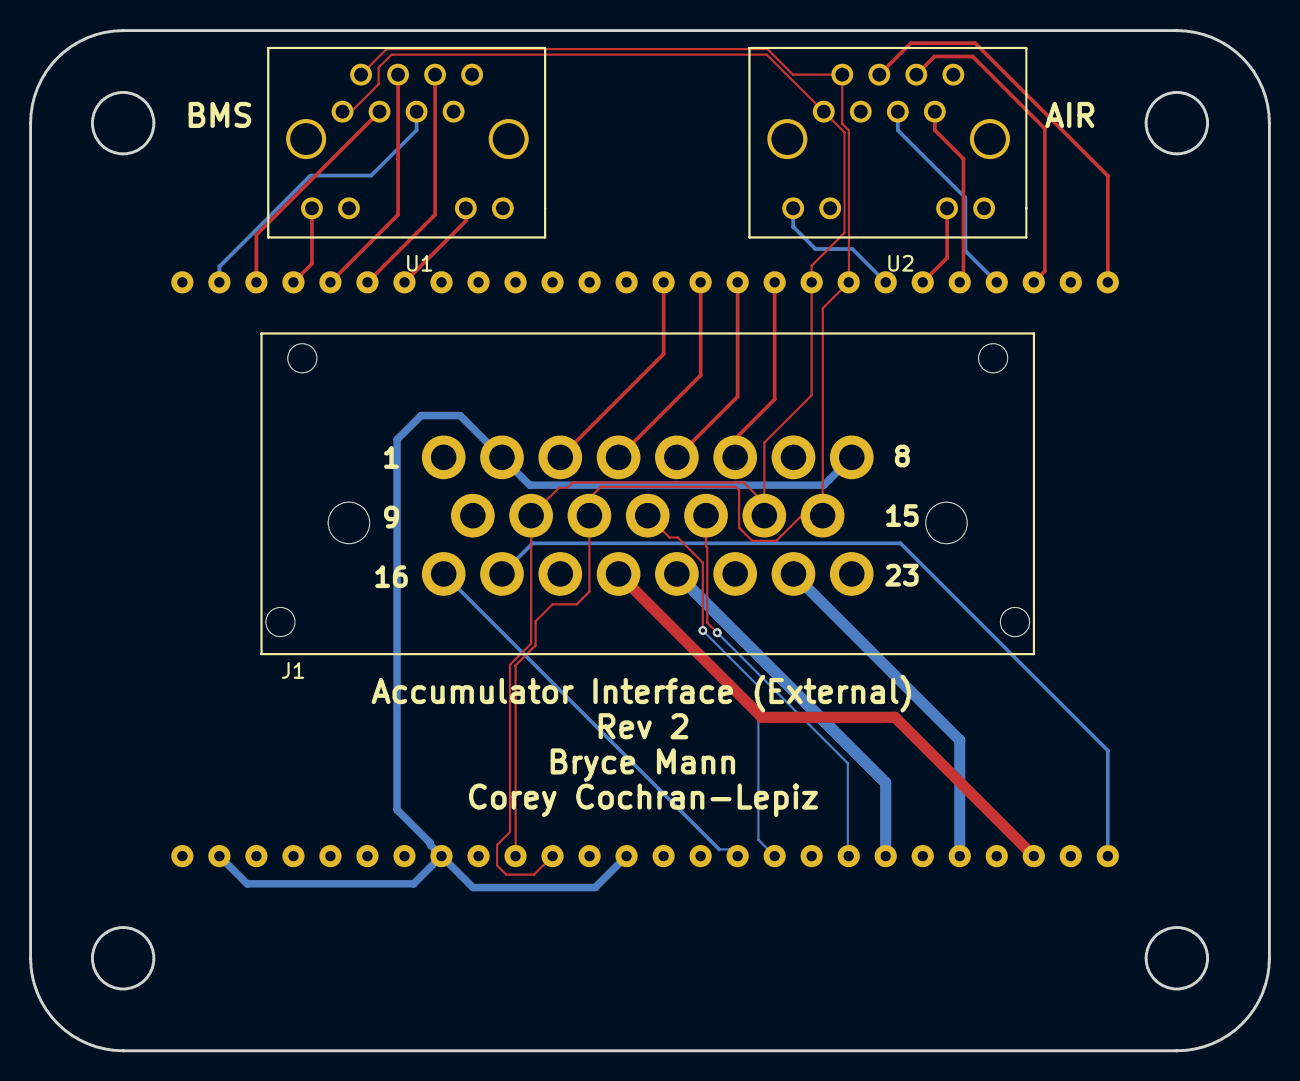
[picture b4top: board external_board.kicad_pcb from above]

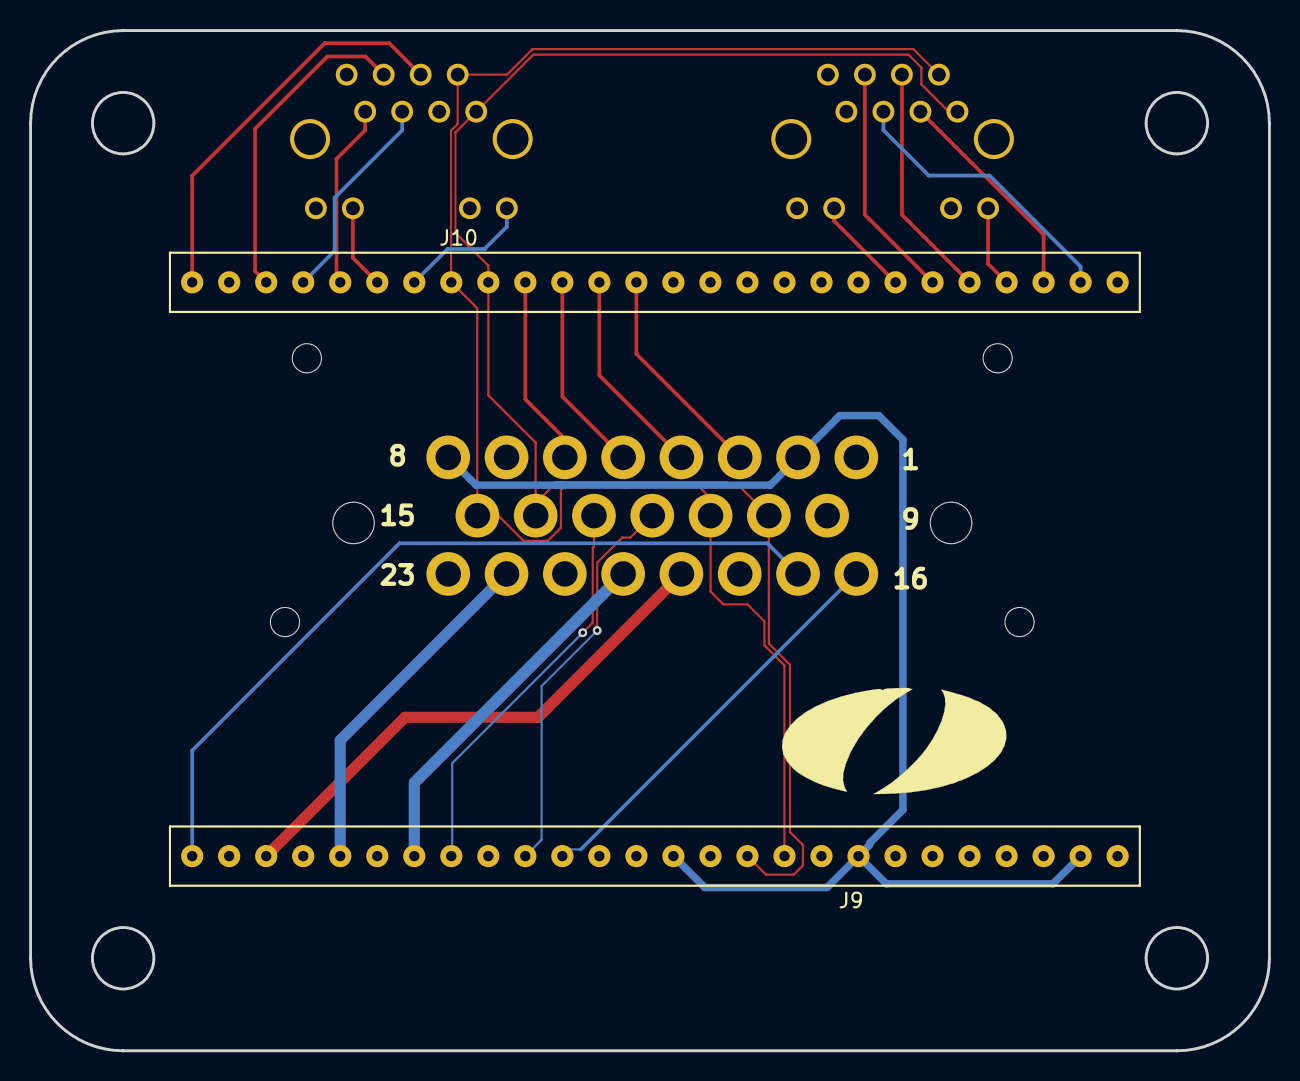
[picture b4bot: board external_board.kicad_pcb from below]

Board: 4 copper layers, 85.0 x 70.0 mm, 5 parts (2 on the bottom side), 30 nets.

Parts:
J1: Ampseal_23_VT; Ampseal_23
J9, J10: SS-126-G-2; 26pos_screwsocket_.1in
U1, U2: RJ45_VT; RJ45-Vertical

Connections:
/5V_AIR: J1.16, J9.16, J10.5, U2.7
/5V_BMS: J10.26, U1.7
/12V: J1.2, J1.8, J9.2, J9.8, J9.13
/BSPD_Current_sense: J1.23, J9.4
/CAN_HIGH: J1.11, J1.15, J9.10, J10.8, U1.2, U2.2
/CAN_LOW: J1.10, J1.14, J9.11, J10.9, U1.1, U2.1
/Cooling_pressure_sense: J1.17, J9.26
/FAN_PWM: J1.21, J9.3
/LED1_AIR: J10.6, U2.10
/LED1_BMS: J10.20, U1.10
/LED2_AIR: J10.7, U2.12
/LED2_BMS: J10.23, U1.12
/MISO_AIR: J10.4, U2.5
/MISO_BMS: J10.25, U1.5
/MOSI_AIR: J10.3, U2.6
/MOSI_BMS: J10.21, U1.6
/RESET_AIR: J10.2, U2.3
/RESET_BMS: J10.24, U1.3
/SCK_AIR: J10.1, U2.4
/SCK_BMS: J10.22, U1.4
/Shutdown_E-STOP: J1.22, J9.22
/Shutdown_Final: J1.20, J9.20
/Shutdown_IMD: J1.19, J9.24
/TSAL+_G: J1.5, J10.11
/TSAL+_R: J1.3, J10.13
/TSAL-_G: J1.6, J10.10
/TSAL-_R: J1.4, J10.12
/emeter_CAN_HIGH: J1.12, J9.17
/emeter_CAN_LOW: J1.13, J9.19
GND: J1.1, J1.7, J1.9, J1.18, J9.1, J9.7, J9.9, J9.12, J9.18, U1.8, U1.9, U1.11, U1.13, U1.14, U2.8, U2.9, U2.11, U2.13, U2.14
